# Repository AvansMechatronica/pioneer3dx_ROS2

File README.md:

# pioneer3dx_ROS2

# [Documentatie](https://avansmechatronica.github.io/pioneer3dx_ROS2/)

[Licentie](licence.md)

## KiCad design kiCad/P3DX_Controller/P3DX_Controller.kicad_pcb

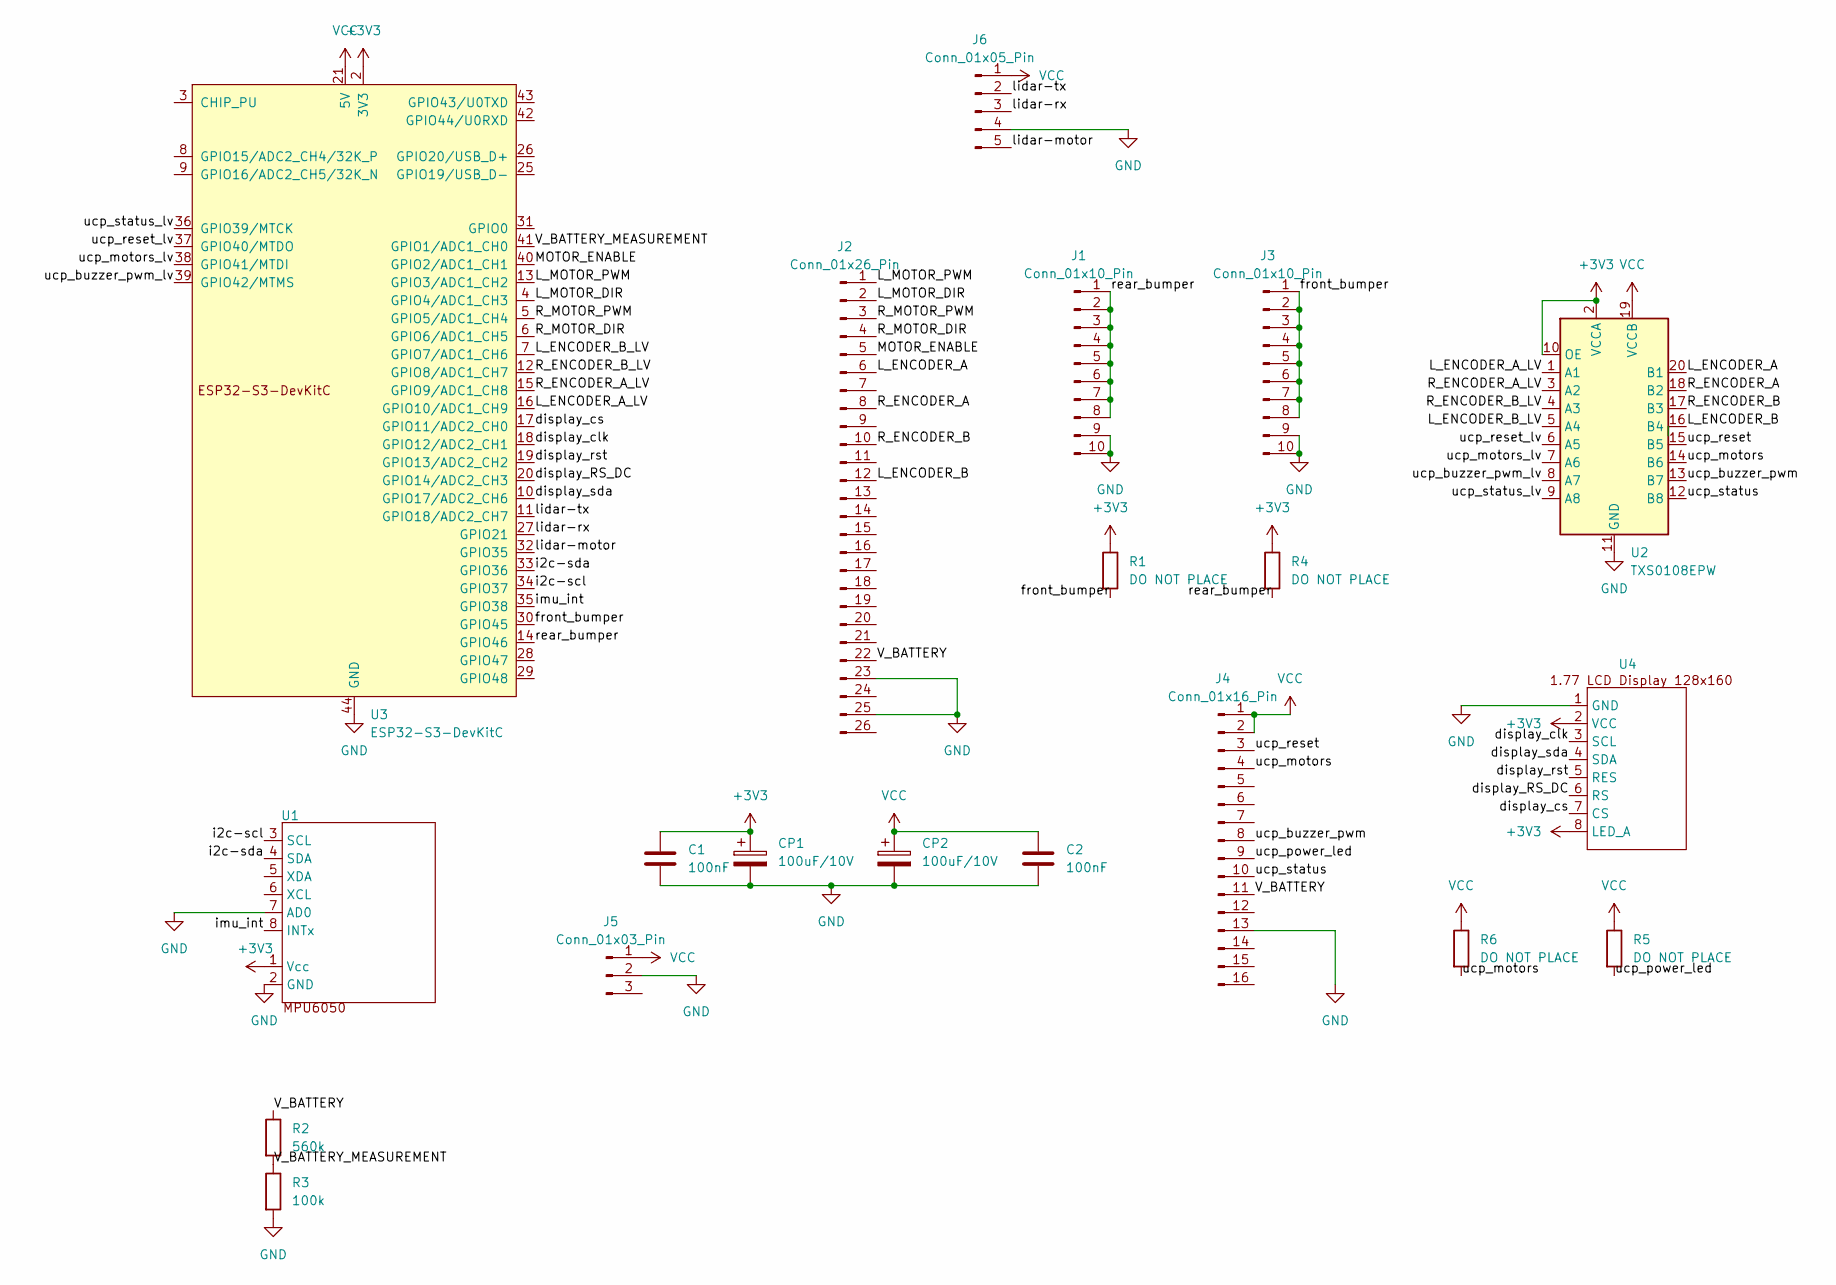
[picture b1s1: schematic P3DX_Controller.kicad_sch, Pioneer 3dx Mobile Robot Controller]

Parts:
C1, C2: 100nF; C_Axial_L3.8mm_D2.6mm_P7.50mm_Horizontal
CP1, CP2: 100uF/10V; CP_Radial_D5.0mm_P2.50mm
J1, J3: Conn_01x10_Pin; IDC-Header_2x05_P2.54mm_Vertical
J2: Conn_01x26_Pin; IDC-Header_2x13_P2.54mm_Vertical
J4: Conn_01x16_Pin; IDC-Header_2x08_P2.54mm_Vertical
J5: Conn_01x03_Pin; PinHeader_1x03_P2.54mm_Vertical
J6: Conn_01x05_Pin; PinHeader_1x05_P2.54mm_Vertical
R1, R4, R5, R6: DO NOT PLACE; R_Axial_DIN0204_L3.6mm_D1.6mm_P7.62mm_Horizontal
R2: 560k; R_Axial_DIN0204_L3.6mm_D1.6mm_P7.62mm_Horizontal
R3: 100k; R_Axial_DIN0204_L3.6mm_D1.6mm_P7.62mm_Horizontal
U1: MPU6050
U2: TXS0108EPW; Texas_TXS0108E_Level_Shifter_Module
U3: ESP32-S3-DevKitC
U4: 1.77 LCD Display 128x160

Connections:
+3V3: C1.1, CP1.1, R1.1, R4.1, U1.1 (Vcc), U2.2 (VCCA), U2.10 (OE), U3.1 (3V3), U3.2 (3V3), U4.2 (VCC), U4.8 (LED_A)
/L_ENCODER_A: J2.6, U2.20 (B1)
/L_ENCODER_A_LV: U2.1 (A1), U3.16 (GPIO10/ADC1_CH9)
/L_ENCODER_B: J2.12, U2.16 (B4)
/L_ENCODER_B_LV: U2.5 (A4), U3.7 (GPIO7/ADC1_CH6)
/L_MOTOR_DIR: J2.2, U3.4 (GPIO4/ADC1_CH3)
/L_MOTOR_PWM: J2.1, U3.13 (GPIO3/ADC1_CH2)
/MOTOR_ENABLE: J2.5, U3.40 (GPIO2/ADC1_CH1)
/R_ENCODER_A: J2.8, U2.18 (B2)
/R_ENCODER_A_LV: U2.3 (A2), U3.15 (GPIO9/ADC1_CH8)
/R_ENCODER_B: J2.10, U2.17 (B3)
/R_ENCODER_B_LV: U2.4 (A3), U3.12 (GPIO8/ADC1_CH7)
/R_MOTOR_DIR: J2.4, U3.6 (GPIO6/ADC1_CH5)
/R_MOTOR_PWM: J2.3, U3.5 (GPIO5/ADC1_CH4)
/V_BATTERY: J2.22, J4.11, R2.1
/V_BATTERY_MEASUREMENT: R2.2, R3.1, U3.41 (GPIO1/ADC1_CH0)
/display_RS_DC: U3.20 (GPIO14/ADC2_CH3), U4.6 (RS)
/display_clk: U3.18 (GPIO12/ADC2_CH1), U4.3 (SCL)
/display_cs: U3.17 (GPIO11/ADC2_CH0), U4.7 (CS)
/display_rst: U3.19 (GPIO13/ADC2_CH2), U4.5 (RES)
/display_sda: U3.10 (GPIO17/ADC2_CH6), U4.4 (SDA)
/front_bumper: J3.1, J3.2, J3.3, J3.4, J3.5, J3.6, J3.7, J3.8, R1.2, U3.30 (GPIO45)
/i2c-scl: U1.3 (SCL), U3.34 (GPIO37)
/i2c-sda: U1.4 (SDA), U3.33 (GPIO36)
/imu_int: U1.8 (INTx), U3.35 (GPIO38)
/lidar-motor: J6.5, U3.32 (GPIO35)
/lidar-rx: J6.3, U3.27 (GPIO21)
/lidar-tx: J6.2, U3.11 (GPIO18/ADC2_CH7)
/rear_bumper: J1.1, J1.2, J1.3, J1.4, J1.5, J1.6, J1.7, J1.8, R4.2, U3.14 (GPIO46)
/ucp_buzzer_pwm: J4.8, U2.13 (B7)
/ucp_buzzer_pwm_lv: U2.8 (A7), U3.39 (GPIO42/MTMS)
/ucp_motors: J4.4, R6.2, U2.14 (B6)
/ucp_motors_lv: U2.7 (A6), U3.38 (GPIO41/MTDI)
/ucp_power_led: J4.9, R5.2
/ucp_reset: J4.3, U2.15 (B5)
/ucp_reset_lv: U2.6 (A5), U3.37 (GPIO40/MTDO)
/ucp_status: J4.10, U2.12 (B8)
/ucp_status_lv: U2.9 (A8), U3.36 (GPIO39/MTCK)
GND: C1.2, C2.2, CP1.2, CP2.2, J1.9, J1.10, J2.23, J2.25, J3.9, J3.10, J4.13, J5.2, J6.4, R3.2, U1.2 (GND), U1.7 (AD0), U2.11 (GND), U3.22 (GND), U3.23 (GND), U3.24 (GND), U3.44 (GND), U4.1 (GND)
VCC: C2.1, CP2.1, J4.1, J4.2, J5.1, J6.1, R5.1, R6.1, U2.19 (VCCB), U3.21 (5V)

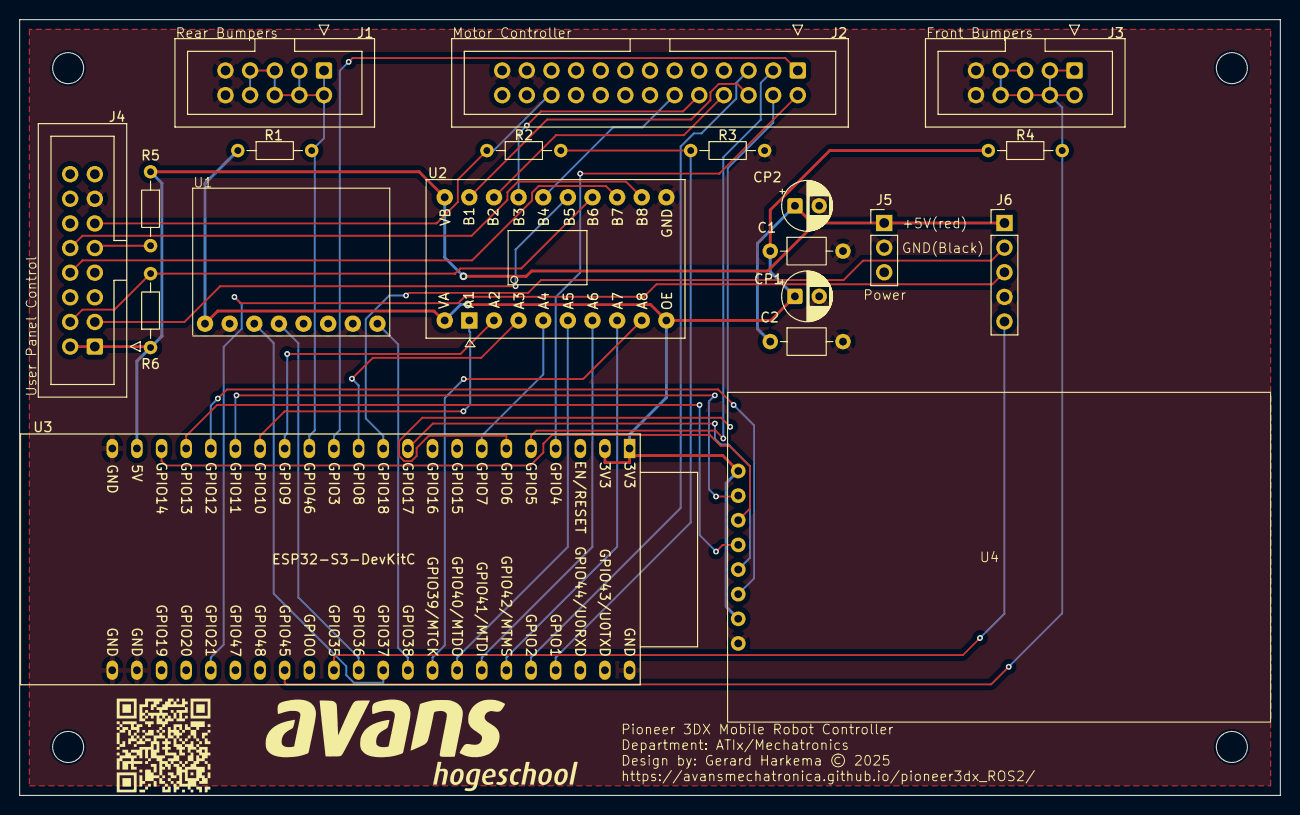
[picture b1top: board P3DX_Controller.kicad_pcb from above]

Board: 2 copper layers, 130.0 x 80.0 mm, 26 parts (0 on the bottom side), 40 nets.

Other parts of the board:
G1, G2: LOGO
HOLE1, HOLE2, HOLE3, HOLE4: MountingHole_3.2mm_M3

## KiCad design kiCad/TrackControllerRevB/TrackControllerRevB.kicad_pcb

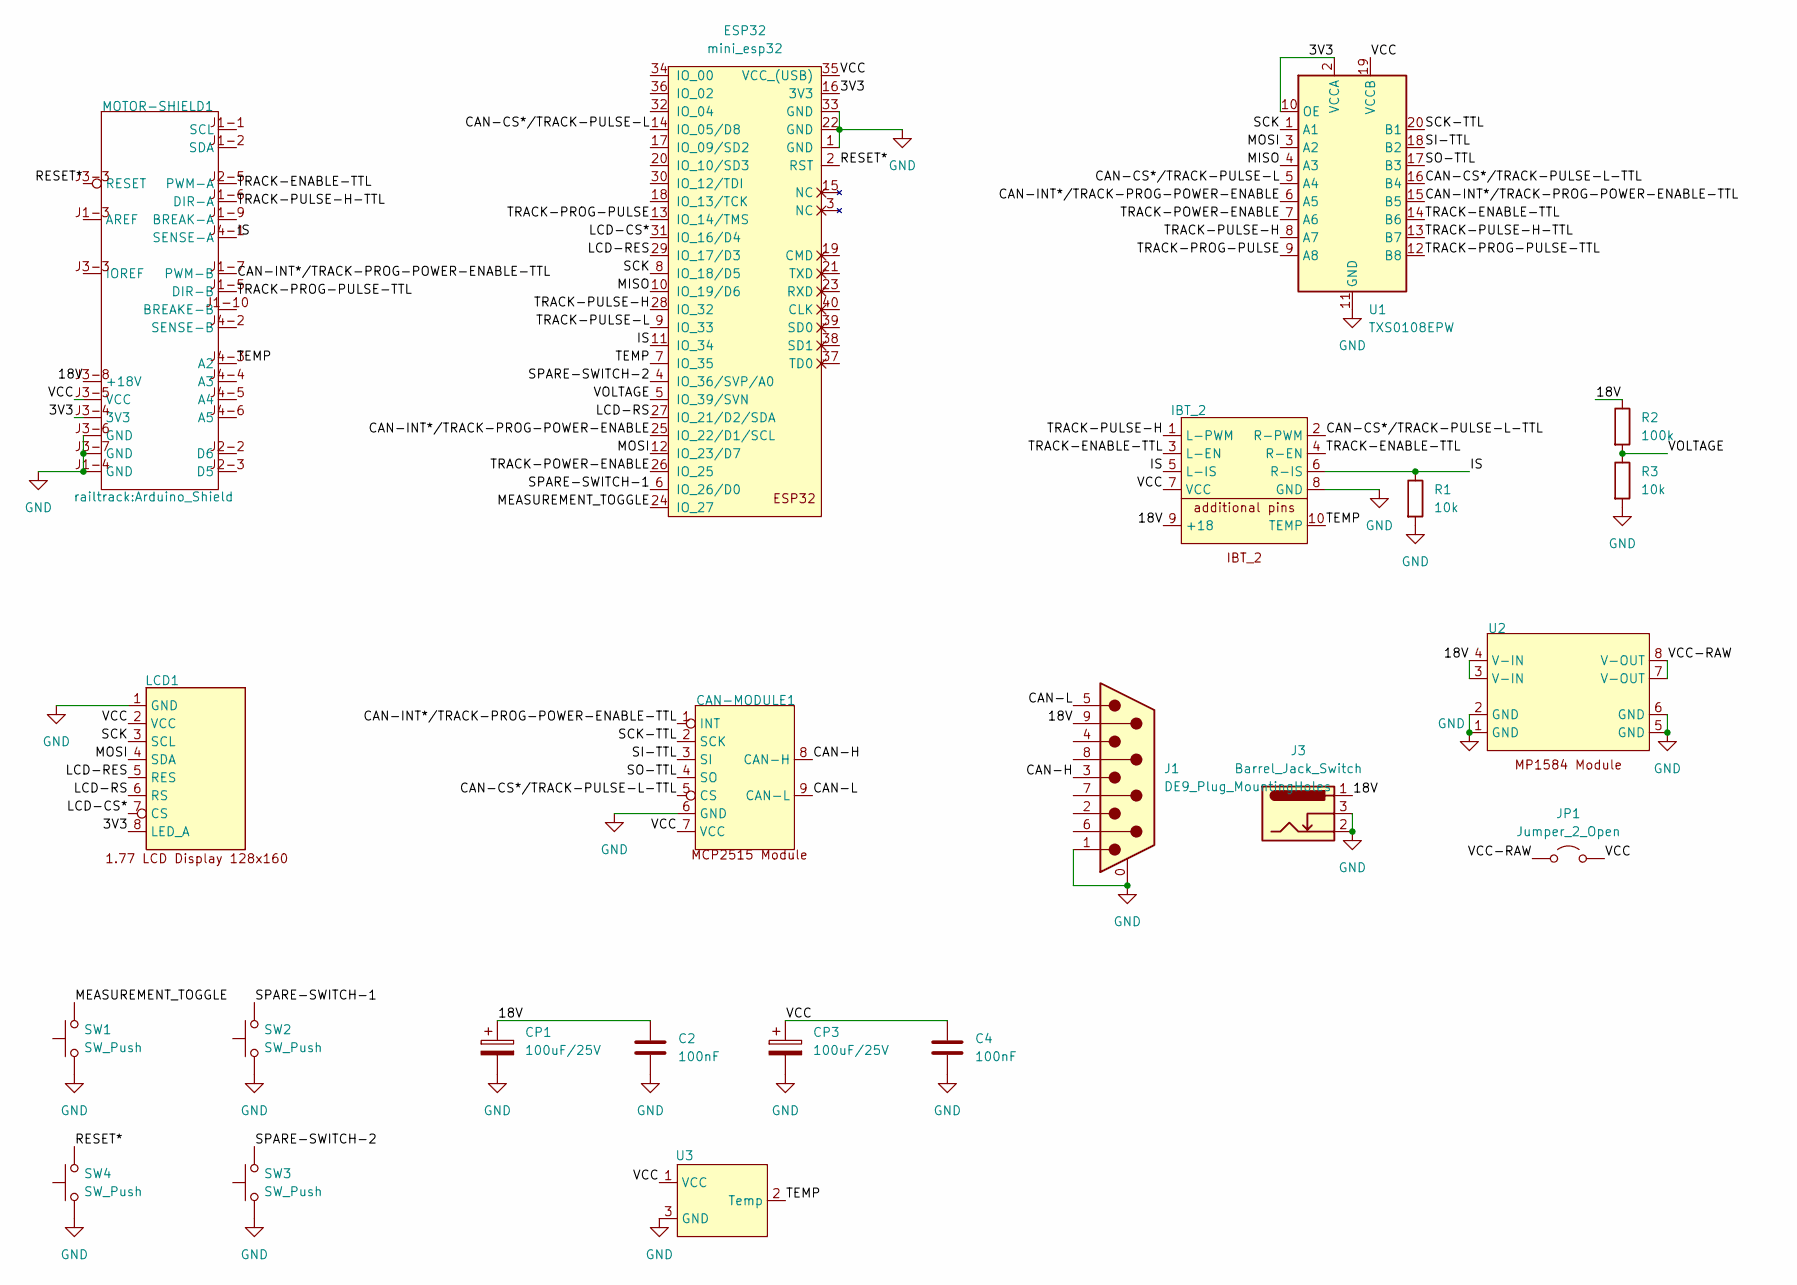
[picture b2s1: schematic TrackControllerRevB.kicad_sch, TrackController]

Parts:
C2, C4: 100nF; C_Disc_D5.1mm_W3.2mm_P5.00mm
CAN-MODULE1: MCP2515 Module
CP1, CP3: 100uF/25V; CP_Radial_D8.0mm_P5.00mm
ESP32: mini_esp32; ESP32_mini
IBT_2: IBT_2
J1: DE9_Plug_MountingHoles; DSUB-9_Male_Horizontal_P2.77x2.84mm_EdgePinOffset4.94mm_Hou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
J3: Barrel_Jack_Switch; BarrelJack_GCT_DCJ200-10-A_Horizontal
JP1: Jumper_2_Open; PinHeader_1x02_P2.54mm_Vertical
LCD1: 1.77 LCD Display 128x160
MOTOR-SHIELD1: Arduino_Shield
R1, R3: 10k; R_Axial_DIN0207_L6.3mm_D2.5mm_P7.62mm_Horizontal
R2: 100k; R_Axial_DIN0207_L6.3mm_D2.5mm_P7.62mm_Horizontal
SW1, SW2, SW3, SW4: SW_Push; SW_PUSH_6mm
U1: TXS0108EPW; Texas_TXS0108E_Level_Shifter_Module
U2: MP1484 Module
U3: TO-92

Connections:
/3V3: ESP32.16 (3V3), LCD1.8 (LED_A), MOTOR-SHIELD1.J3-4 (3V3), U1.2 (VCCA), U1.10 (OE)
/18V: C2.1, CP1.1, IBT_2.9 (+18), J1.9, J3.1, MOTOR-SHIELD1.J3-8 (+18V), R2.1, U2.3 (V-IN), U2.4 (V-IN)
/CAN-CS*/TRACK-PULSE-L: ESP32.14 (IO_05/D8), U1.5 (A4)
/CAN-CS*/TRACK-PULSE-L-TTL: CAN-MODULE1.5 (CS), IBT_2.2 (R-PWM), U1.16 (B4)
/CAN-H: CAN-MODULE1.8 (CAN-H), J1.3
/CAN-INT*/TRACK-PROG-POWER-ENABLE: ESP32.25 (IO_22/D1/SCL), U1.6 (A5)
/CAN-INT*/TRACK-PROG-POWER-ENABLE-TTL: CAN-MODULE1.1 (INT), MOTOR-SHIELD1.J1-7 (PWM-B), U1.15 (B5)
/CAN-L: CAN-MODULE1.9 (CAN-L), J1.5
/IS: ESP32.11 (IO_34), IBT_2.5 (L-IS), IBT_2.6 (R-IS), MOTOR-SHIELD1.J4-1 (SENSE-A), R1.1
/LCD-CS*: ESP32.31 (IO_16/D4), LCD1.7 (CS)
/LCD-RES: ESP32.29 (IO_17/D3), LCD1.5 (RES)
/LCD-RS: ESP32.27 (IO_21/D2/SDA), LCD1.6 (RS)
/MEASUREMENT_TOGGLE: ESP32.24 (IO_27), SW1.2
/MISO: ESP32.10 (IO_19/D6), U1.4 (A3)
/MOSI: ESP32.12 (IO_23/D7), LCD1.4 (SDA), U1.3 (A2)
/RESET*: ESP32.2 (RST), MOTOR-SHIELD1.J3-3 (RESET), SW4.2
/SCK: ESP32.8 (IO_18/D5), LCD1.3 (SCL), U1.1 (A1)
/SCK-TTL: CAN-MODULE1.2 (SCK), U1.20 (B1)
/SI-TTL: CAN-MODULE1.3 (SI), U1.18 (B2)
/SO-TTL: CAN-MODULE1.4 (SO), U1.17 (B3)
/SPARE-SWITCH-1: ESP32.6 (IO_26/D0), SW2.2
/SPARE-SWITCH-2: ESP32.4 (IO_36/SVP/A0), SW3.2
/TEMP: ESP32.7 (IO_35), IBT_2.10 (TEMP), MOTOR-SHIELD1.J4-3 (A2), U3.2 (Temp)
/TRACK-ENABLE-TTL: IBT_2.3 (L-EN), IBT_2.4 (R-EN), MOTOR-SHIELD1.J2-5 (PWM-A), U1.14 (B6)
/TRACK-POWER-ENABLE: ESP32.26 (IO_25), U1.7 (A6)
/TRACK-PROG-PULSE: ESP32.13 (IO_14/TMS), U1.9 (A8)
/TRACK-PROG-PULSE-TTL: MOTOR-SHIELD1.J1-5 (DIR-B), U1.12 (B8)
/TRACK-PULSE-H: ESP32.28 (IO_32), IBT_2.1 (L-PWM), U1.8 (A7)
/TRACK-PULSE-H-TTL: MOTOR-SHIELD1.J1-6 (DIR-A), U1.13 (B7)
/TRACK-PULSE-L: ESP32.9 (IO_33)
/VCC: C4.1, CAN-MODULE1.7 (VCC), CP3.1, ESP32.35 (VCC_(USB)), IBT_2.7 (VCC), JP1.2 (B), LCD1.2 (VCC), MOTOR-SHIELD1.J3-5 (VCC), U1.19 (VCCB), U3.1 (VCC)
/VCC-RAW: JP1.1 (A), U2.7 (V-OUT), U2.8 (V-OUT)
/VOLTAGE: ESP32.5 (IO_39/SVN), R2.2, R3.1
GND: C2.2, C4.2, CAN-MODULE1.6 (GND), CP1.2, CP3.2, ESP32.1 (GND), ESP32.22 (GND), ESP32.33 (GND), IBT_2.8 (GND), J1.0 (PAD), J1.1, J3.2, J3.3, LCD1.1 (GND), MOTOR-SHIELD1.J1-4 (GND), MOTOR-SHIELD1.J3-6 (GND), MOTOR-SHIELD1.J3-7 (GND), R1.2, R3.2, SW1.1, SW2.1, SW3.1, SW4.1, U1.11 (GND), U2.1 (GND), U2.2 (GND), U2.5 (GND), U2.6 (GND), U3.3 (GND)

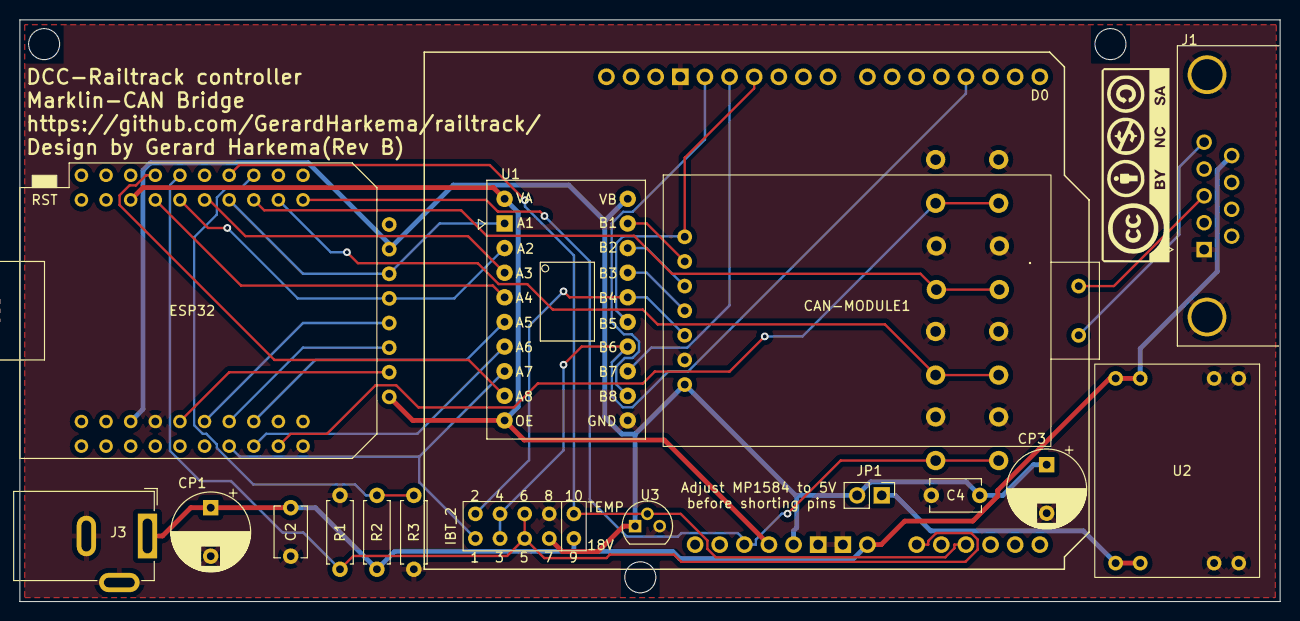
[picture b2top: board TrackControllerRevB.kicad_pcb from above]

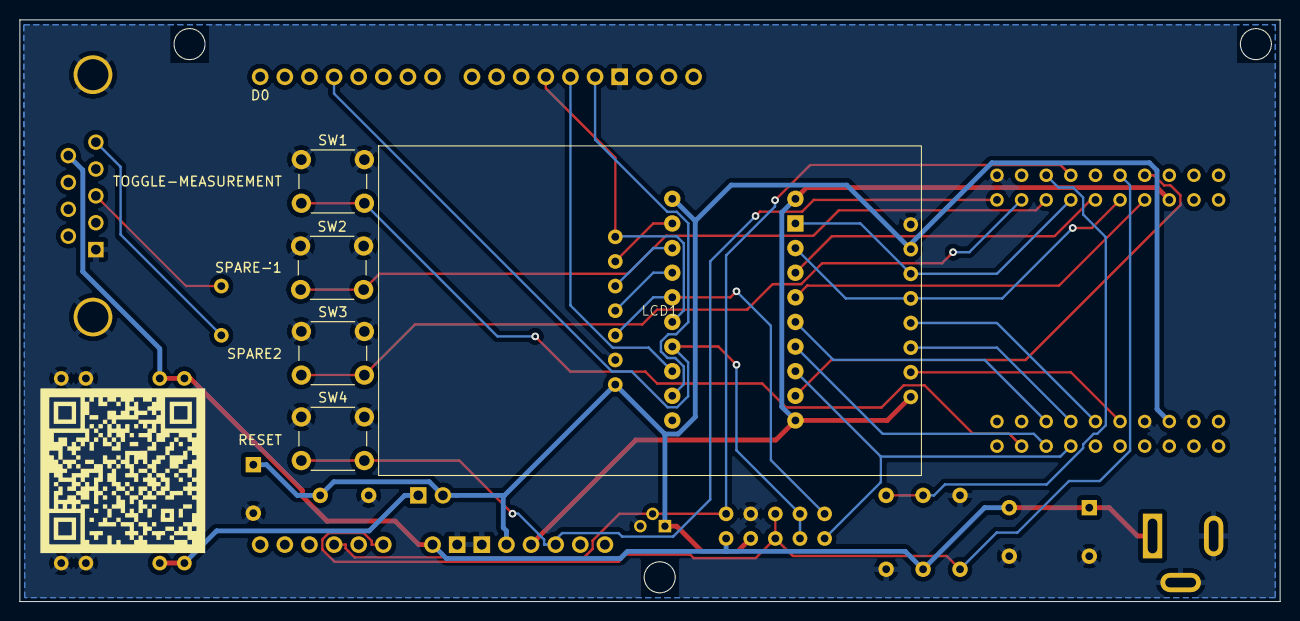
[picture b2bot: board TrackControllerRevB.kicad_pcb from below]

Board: 2 copper layers, 130.0 x 60.0 mm, 23 parts (5 on the bottom side), 33 nets.

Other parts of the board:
G1: LOGO

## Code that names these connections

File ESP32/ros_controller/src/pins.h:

#ifndef PINS_H
#define PINS_H

//pin declaration
//Left wheel
#define L_PWM_PIN        3
#define L_DIR_PIN        4
#define PWM_CHANNEL_LEFT 0
#define L_ENCODER_PINA   10 //Encoder Output of pin1 must connected with intreput pin of Esp32.
#define L_ENCODER_PINB   7
//right wheel
#define R_PWM_PIN        5
#define R_DIR_PIN        6
#define PWM_CHANNEL_RIGHT 1
#define R_ENCODER_PINA   9  //Encoder Output of pin1 must connected with intreput pin of Esp32.
#define R_ENCODER_PINB   8




#if defined(HANDLE_BUMPERS)
#define BUMPER_FRONT_PIN    45
#define BUMPER_REAR_PIN     46
#endif


#define MOTOR_ENABLE_PIN    2
#define MOTOR_ENABLE        LOW
#define MOTOR_DISABLE       HIGH 

//#define SELECT_WIFI_CONFIG_MODE_PIN 13

#define DISPLAY_CS_PIN    11
#define DISPLAY_RS_DC_PIN 14
#define DISPLAY_RST_PIN   13
#define DISPLAY_CLK_PIN   12
#define DISPLAY_SDA_PIN   17
//#define DISPLAY_MISO_PIN  19 // Not used

#define LIDAR_COM_PORT    1      
#define LIDAR_TX_PIN      18 // Lidar side

#define LIDAR_RX_PIN      21 // Lidar side
#define LIDAR_MOTOR_PIN   35 // optioneel: PWM of GPIO voor motor aan/uit

#define UCP_STATUS_PIN      39 // Pin to read UCP status
#define UCP_RESET_PIN       40 // Pin to reset UCP
#define UCP_MOTORS_PIN      41 // Pin to control UCP motor power
#define UCP_BUZZER_PIN      42 // Pin to control UCP buzzer
#define UCP_BUZZER_PWM_CHANNEL  2 // PWM channel for UCP buzzer (must not overlap motor channels)

#define I2C_SDA_PIN  36 //  
#define I2C_SCL_PIN  37 // 
#define IMU_INT_PIN  38 // Interrupt pin from IMU

#define LED_PIN 2

#define BATTERY_VOLTAGE_PIN 1 // ADC pin to read battery voltage

#endif

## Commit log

2025-10-21 20251021
2025-10-21 added lidar
2025-10-22 20251022
2025-10-23 20251013
2025-10-24 added jazzy
2025-10-24 20251014
2025-10-24 20251024
2025-10-24 20251024-2
2025-10-25 202251025
2025-10-28 20251028
2025-10-29 20251029
2025-10-29 20241029
2025-10-30 20251030
2025-10-31 20251031
2025-11-01 20251101
2025-11-02 20251102
2025-11-02 Added documentation
2025-11-03 20251103
2025-11-04 20251104
2025-11-05 20251105
2025-11-06 20251106
2025-11-07 20251107
2025-11-09 20251109
2025-11-10 20251110
2025-11-13 20251113
2025-11-15 20251115
2025-11-16 20251116
2025-11-17 20251117
2025-11-18 20251118
2025-11-21 linorobot inspiratie
2025-11-23 20251123
2025-11-24 20251124
2025-11-25 20251125
2025-11-27 20251127
2025-11-27 20251128
2025-11-29 20251129
2025-11-30 20251130
2025-12-01 20251201
2025-12-02 20251202
2025-12-03 20251203
2025-12-03 esp32-s3 change
2025-12-04 20251204
2025-12-05 20251205
2025-12-07 20251207
2025-12-07 added imu
2025-12-07 added FreCad Lidar & Display carrier
2025-12-09 20251209
2025-12-10 20251210
2025-12-11 20251211
2025-12-14 20251114
2025-12-16 Change to ESP32-S3
2025-12-17 20251217
2025-12-20 20251220
2025-12-23 20251223
2025-12-23 added buzzer
2025-12-24 20251224
2025-12-24 added monitor gui
2025-12-31 20251231
2026-01-01 20260101
2026-01-03 Cleanup main.c
2026-01-03 added command timeout
2026-01-03 20260102
2026-01-04 20260104
2026-01-07 20260107
2026-01-08 20260108
2026-01-13 20250113
2026-01-25 20260126
2026-01-27 repair tests IMU
2026-02-15 20260215
2026-02-17 20260217
2026-02-19 20260219
2026-02-25 20260225
2026-02-28 20260301
2026-03-02 20260302
2026-03-12 added ydlidar testing
2026-03-13 20260313
2026-03-14 20260314
2026-03-15 20260315
2026-04-15 20260415
2026-04-17 20260417
2026-04-18 20260418
2026-04-18 2020260418
2026-04-20 20260420
2026-04-21 20260421
2026-05-21 20260621
2026-06-08 20260608
2026-06-08 deploy: 4a46c6828352d9371a0d3ab7c96a21771a27b8ce

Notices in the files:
kiCad/P3DX_Controller/P3DX_Controller.kicad_pcb:
Design by: Gerard Harkema © 2025
